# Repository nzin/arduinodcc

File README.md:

View this project on [CADLAB.io](https://cadlab.io/node/817). 

A versatile Arduino stationary dcc decoder
==========================================

When constructing my dcc based train model, I looked for dcc decoder to pilot light (SMD 0402, or standard led), but had difficulty to program them for custom scenario (blinking, road works style, …). There are also some DIY dcc decoder (opendcc decoder) but didn’t manage to make them working. So I decided to create my own stationary dcc decoder based on Arduino (nano), to be able to reprogram it at wish.

This decoder is pretty simple, you can
 * assign it a dcc address (via a learning switch button)
 * connect LED lights, or a relay
 * choose the light mode if you connected lights. There are 3 different modes you can choose via a push button: constant light (on or off), flicker mode, or 3 way road work lights mode

It has been designed to be powered by a 16V AC, but can be as well be powered via DCC signal (15v or 18v), or a DC signal.

Using it
========

Powering
--------
This decoder is designed to be powered by a 16V AC power source. It is possible to power it with the dcc signal, but my circuit is not the most power efficient stationary decoder (due to the fact that it power lights, an arduino and eventually a relay), so you don’t want that, except in rare situation.

This is why there are 2 set of cables:
 * one for the 16V AC
 * one for the DCC signal

Assign a dcc address
--------------------

To assign a dcc address, you have to use the learning switch opposite to the Arduino.
In that position, each time it see a stationary decoder command coming on, it will store it as its new address (and will acknowledge that by blinking the status led).
So to assign a dcc address you just have to
 * push the learning switch opposite to the Arduino.
 * send a command with the wished address
 * you will see the status led blinking, stating that it saw the address and learned it
 * push back the learning switch towards the Arduino

Connect light
-------------

On the bottom of the card, you have 3 slots for leds. The + of the led must be on the left. Normaly you can connect only one led per slot (due to the nominal tension that each led has, 2 different led don't have the exact same nominal tension).

If you use the push button, you will circle between 3 modes:
 * constantly on (or off)
 * flickering seldomly
 * 3 way road work lights (it will switch on the first light, then the second light, then the 3rd light, and cycle again to the first light)

You just has to use the push button to cycle between the 3 modes. The little status led, will tell you in which mode you are.

Connect relay
-------------

Close to the lights there is a block of 3 pins for the relay (if you decide to build it), which are in this order: low ouput, input, high output.
So the one on the middle is your input (whatever your input is), and the relay will connect it either to the left pin or to the right pin.

Connect to the other IO
=======================

There are some generic IO available, that expose
 * 5v and ground
 * analog pins 6 and 7
 * and digital pins 6 and 7

You can use them at your own advantage, but you will need to reprogram the Arduino to you own purpose: I didn’t program anything on them.

Assemble it
===========

If you don’t want to assemble, or just want the PCB already fabricated, contact me, and I can provide it for you: nicolas.zin@gmail.com

If you prefer to fully assemble it, you will need to get the PCB, and of course the components.
The PCB gerber files are here: https://github.com/nzin/arduinodcc/blob/master/arduinov1.3.zip (for the eagle source check below)

To fully assemble it, the full Bill Of Material is:

item                    |how many |ref
------------------------|---------|------------------------------------
arduino nano            |1        |aliexpress
bridge rectifier        |1        |mouser 625-B40C800G-E4 (or 625-B380C800G-E4)
capa 330uF              |1        |mouser 667-EEU-FM1C331
capa 10uF               |1        |mouser 581-TAP106K025SCS
DC-DC converter (9VDC)  |1        |mouser 490-V7809-1000 (or cheaper: voltage regulator mouser 511-L7809CV but buy also a heatsink!!)
R 50 ohm                |1        |mouser 71-CPF150R000FEE14
relay                   |1        |sparkfun COM-00100
diode 4004              |1        |mouser 512-1N4004 (or 625-1N4004-E3/54)
transistor 2n2222       |1        |mouser 610-2N2222
R 10k ohm               |5        |mouser 71-CCF50-10K
R 1k ohm                |1        |mouser 603-CFR-12JR-521K
diode 4148              |1        |mouser 512-1N4148
toggle button           |1        |sparkfun COM-00102 (maybe mouser 633-SS12SDP2)
push button             |1        |SPARKUN COM-00097 (ou mouser 693-1301.9308)
led                     |1        |mouser 941-C4SMFRJSCT0W0BB2 (or mouser 630-HLMP-1301)
terminal block 2 pos    |8        |mouser 651-1729128
terminal block 3 pos    |1        |mouser 651-1729131
headers                 |2        |mouser 855-M20-7821546
high speed optocoupler  |1        |mouser 630-6N137-000E
R 200 ohm               |4        |mouser 71-CCF50-200
shottky diode           |1        |mouser 833-SR108-TP

Reprogram it
============

If you are familiar with Arduino programming, you can re-program it to whatever needs you have. That the beauty of it. Here are the arduino sources: https://github.com/nzin/arduinodcc/blob/master/arduinoSource/dccduino.ino

It is based on the dcc decoder library from Minabay: https://github.com/MynaBay/DCC_Decoder (included in the arduinoSource/dccduino directory)

Extend it
=========

If you want to develop your own dcc decoder, I provide you the eagle source: https://github.com/nzin/arduinodcc/blob/master/arduinoDcc1.3.sch and https://github.com/nzin/arduinodcc/blob/master/arduinoDcc1.3.brd

Feel free to adapt it to your needs, but I provide it as is, i.e. I can answer some question but if you decide to change the layout, you are on your own

Licence
=======
The Arduino code and the Eagle schema are under the [GPL v2](https://github.com/nzin/arduinodcc/blob/master/gpl-2.0.txt)

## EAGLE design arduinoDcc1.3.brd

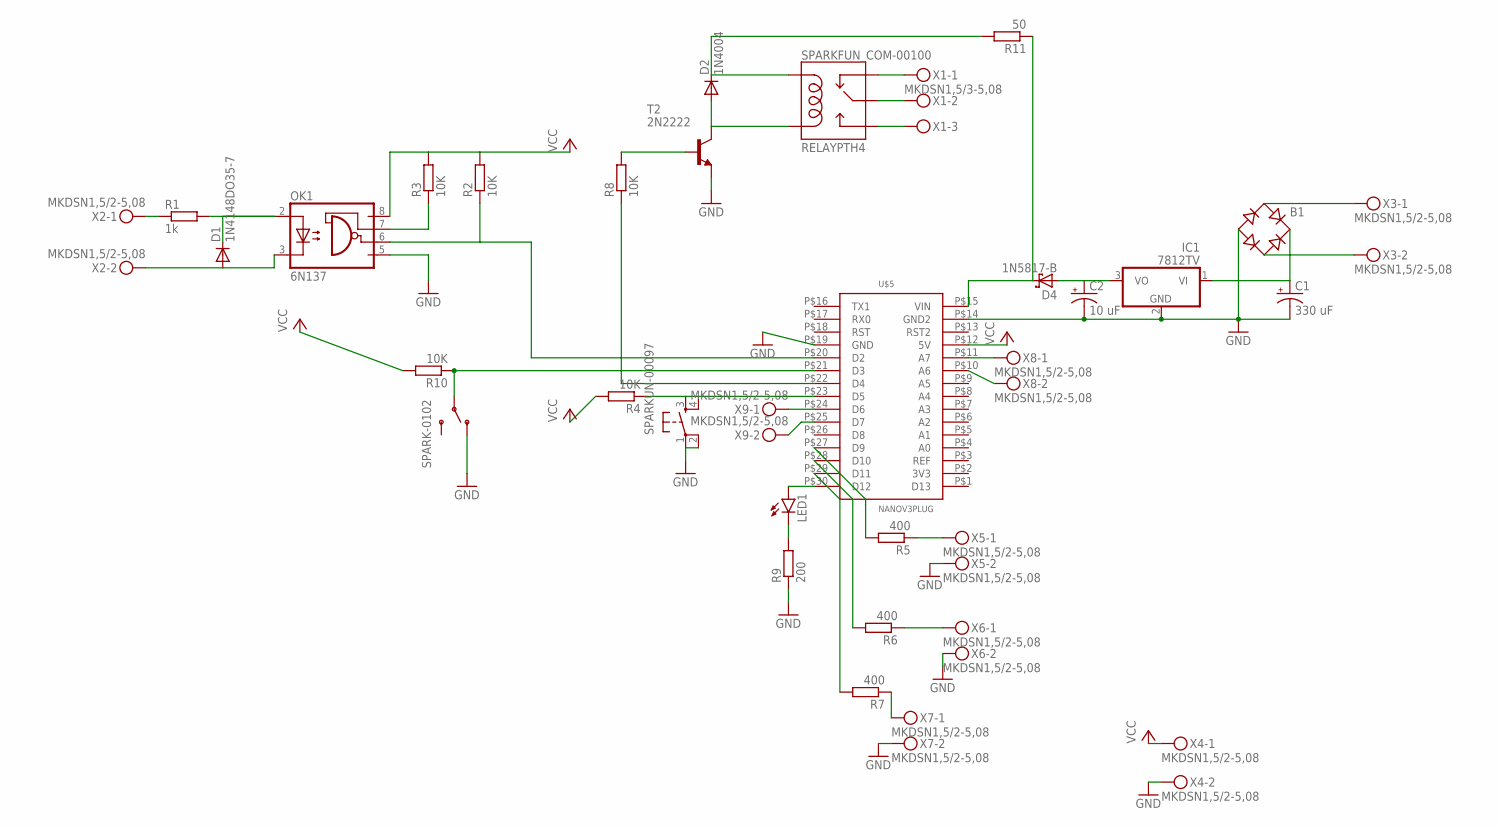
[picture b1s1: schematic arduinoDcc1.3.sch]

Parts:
B1: RB1A
C1: 330 uF; CPOL-RADIAL-100UF-25V
C2: 10 uF; CPOL-RADIAL-100UF-25V
D1: 1N4148DO35-7; DO35-7
D2: 1N4004; DO41-10
D4: 1N5817-B; DO41-7.6
IC1: 7812TV; TO220V
LED1: LED3MM
OK1: 6N137; DIL08
R1: 1k; 0207/10
R2, R3, R4, R8, R10: 10K; 0207/10
R5, R6, R7: 400; 0207/10
R9: 200; 0204/7
R11: 50; 0207/10
SPARK-0102: SWITCH-SPDTPTH; SWITCH-SPDT
SPARKFUN_COM-00100: RELAYPTH4; RELAY-JZC
SPARKUN-00097: TAC_SWITCHPTH; TACTILE-PTH
T2: 2N2222; TO18
U$5: NANOV3PLUG; HEADER15-2
X1: MKDSN1,5/3-5,08
X2, X3, X4, X5, X6, X7, X8, X9: MKDSN1,5/2-5,08

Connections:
GND: B1.-, C1.2 (-), C2.2 (-), IC1.2 (GND), OK1.5 (GND), R9.1, SPARK-0102.1 (O), SPARKUN-00097.1, SPARKUN-00097.2, T2.1 (E), U$5.P$14 (GND2), U$5.P$19 (GND), X4.2, X5.2, X6.2, X7.2
unnamed: R1.1, X2.1
unnamed: D1.C, OK1.2 (A), R1.2
unnamed: D1.A, OK1.3 (C), X2.2
unnamed: R10.1, SPARK-0102.2, U$5.P$21 (D3)
unnamed: D2.A, SPARKFUN_COM-00100.1 (COIL2), T2.3 (C)
unnamed: OK1.6 (VO), R2.1, U$5.P$20 (D2)
unnamed: OK1.7 (VE), R3.1
unnamed: B1.AC1, X3.1
unnamed: SPARKFUN_COM-00100.2 (NC), X1.1
unnamed: SPARKFUN_COM-00100.4 (MAIN), X1.2
unnamed: SPARKFUN_COM-00100.3 (NO), X1.3
unnamed: R8.1, U$5.P$22 (D4)
unnamed: R6.1, X6.1
unnamed: R7.2, U$5.P$29 (D11)
unnamed: R6.2, U$5.P$28 (D10)
unnamed: R5.2, U$5.P$27 (D9)
unnamed: R5.1, X5.1
unnamed: R4.1, SPARKUN-00097.3, SPARKUN-00097.4, U$5.P$23 (D5)
unnamed: U$5.P$24 (D6), X9.1
unnamed: U$5.P$25 (D7), X9.2
unnamed: U$5.P$11 (A7), X8.1
unnamed: U$5.P$10 (A6), X8.2
unnamed: B1.AC2, X3.2
unnamed: B1.+, C1.1 (+), IC1.1 (VI)
unnamed: LED1.K (C), R9.2
unnamed: LED1.A, U$5.P$30 (D12)
unnamed: R7.1, X7.1
unnamed: C2.1 (+), D4.A, IC1.3 (VO)
unnamed: R8.2, T2.2 (B)
unnamed: D2.C, R11.2, SPARKFUN_COM-00100.5 (COIL1)
unnamed: D4.C, R11.1, U$5.P$15 (VIN)
VCC: OK1.8 (VCC), R2.2, R3.2, R4.2, R10.2, U$5.P$12 (5V), X4.1

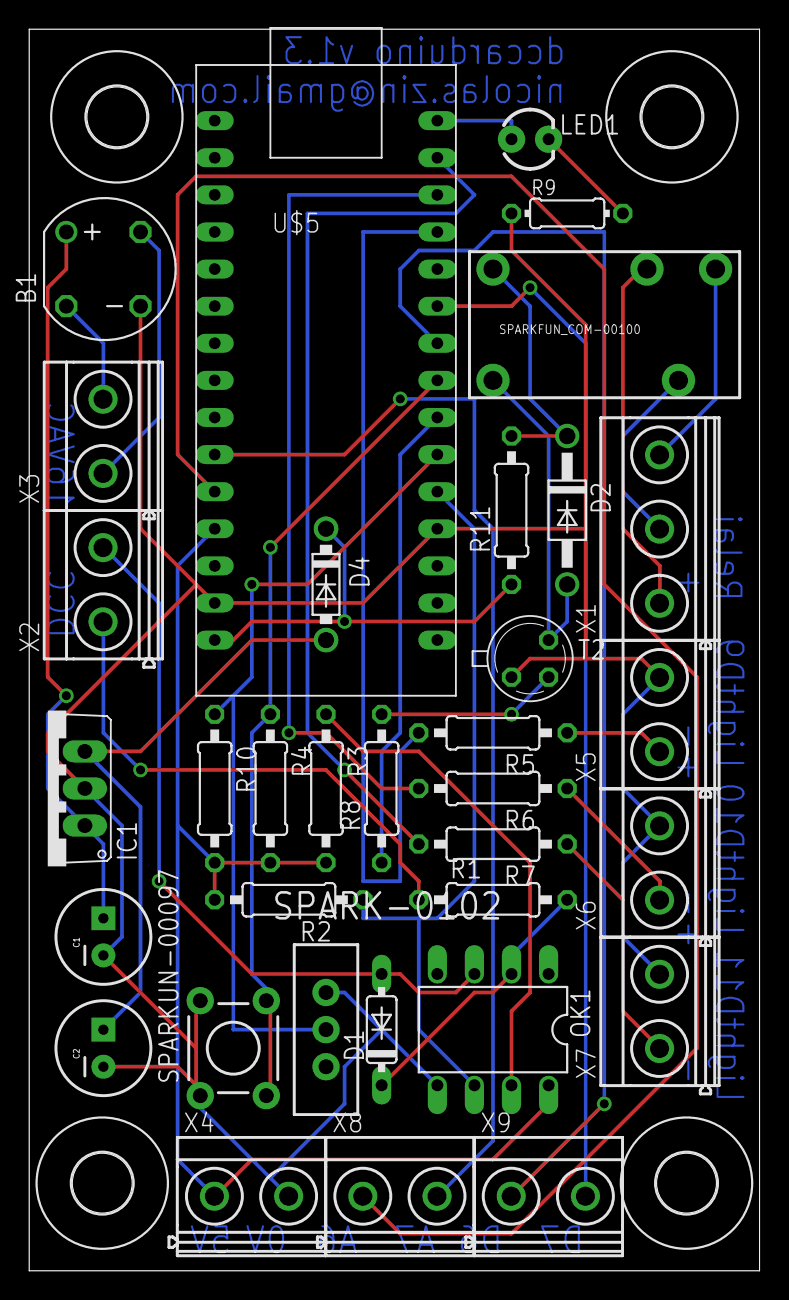
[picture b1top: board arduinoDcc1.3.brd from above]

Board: 2 copper layers, 50.0 x 85.0 mm, 38 parts (0 on the bottom side), 33 nets.

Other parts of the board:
U$1, U$2, U$3, U$4: 4,1

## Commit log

2015-01-03 add beginning of doc
2015-01-03 more doc
2015-01-03 add licence
2015-01-03 add Readme for ReadTheDoc
2015-01-04 update doc schema
2015-01-05 typo
2015-06-07 put hardlink
2015-06-07 put hardlink 3
2016-02-02 test
2016-02-02 add docs for RTD
2016-06-02 forgot to mention a 200 ohm resistor
2016-06-02 point to the new mynabay git repo
2016-06-02 rename the directory to fit with new Arduino tool
2016-07-02 add other reference for terminal block
2016-07-09 change voltage regulator to swtiching power supply
2016-07-30 new version 1.3, with DC-DC converter instead of voltage regulator
2016-09-05 fix ref to optocoupler: Mouser don't have some ref in stock
2016-11-04 forgot to mention the shottky diode
2017-01-06 only one shottky diode
2017-02-08 refresh bom
2018-03-09 update BOM
2018-03-11 update documentation regarding mynabay
2018-03-11 update documentation
2018-03-11 update readthedocs documentation
2018-03-11 update all links
2018-04-02 Backlink to CADLAB.io has been added.

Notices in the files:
parts and their libraries:
SparkFun-Electromechanical: Licensing: Creative Commons ShareAlike 4.0 International - https://creativecommons.org/licenses/by-sa/4.0
